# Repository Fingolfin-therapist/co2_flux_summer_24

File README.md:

# Wildfire CO<sub>2</sub> Flux Project - Summer 2024

This directory includes scripts and data for the 2024 Summer Wildfire CO<sub>2</sub> Flux Project. Please see the repository structure section below.

# Repository Structure

|Folder|Description|
|----|----|
|ELT CALIBRATION|Scripts for calibrating ELT S300-3V CO<sub>2</sub> sensors. Ambient colocations are used for ambient sensors. Ambient and closed loop colocations are used for ambient sensors.|
|FLUXES|Scripts for calculating fluxes from datasets.|
|LICOR|Calibration files for LICOR LI-7810.|
|MFC|Calibration and control scripts for Mass Flow Controller (MFC).|
|MODELING|Theoretical applications of box model.|
|DAQ|Hardware and firmware for data acquisition system (DAQ).|

# Contributing

To ensure smooth collaboration and avoid unnecessary merge requests, please follow these simple steps for contribution:

1) Fork the Repository
    - Click the Fork button at the top right of this repository page to create a copy of the repository under your GitHub account.
2) Clone Your Fork
    - Clone your forked repository to your local machine:
    - `git clone https://github.com/BikeLinc/co2_flux_summer_24.git`
    - `cd your-repo`
3) Create a New Branch
    - Create a new branch for your work. Name your branch based on the feature or issue you are working on:
    - `git checkout -b feature/your-feature-name`
4) Make Your Changes
    - Make your changes to the code.
5) Commit Your Changes
    - Commit your changes with a clear and concise commit message:
    - `git add .`
    - `git commit -m "Add description of changes"`
6) Push Your Branch
    - Push your branch to your forked repository:
    - `git push origin feature/your-feature-name`
7) Open a Pull Request
    - Go to the original repository on GitHub. You should see a prompt to open a pull request. Click on it and provide a clear description of your changes.
8) Wait for Review
    - Your pull request will be reviewed. Make any necessary changes based on feedback.

For an extensive guide to git and GitHub, see [GitHub's Git Guide](https://github.com/git-guides).

# Questions

Please email Lincoln (lascheer@fortlewis.edu) for any questions about this repository.

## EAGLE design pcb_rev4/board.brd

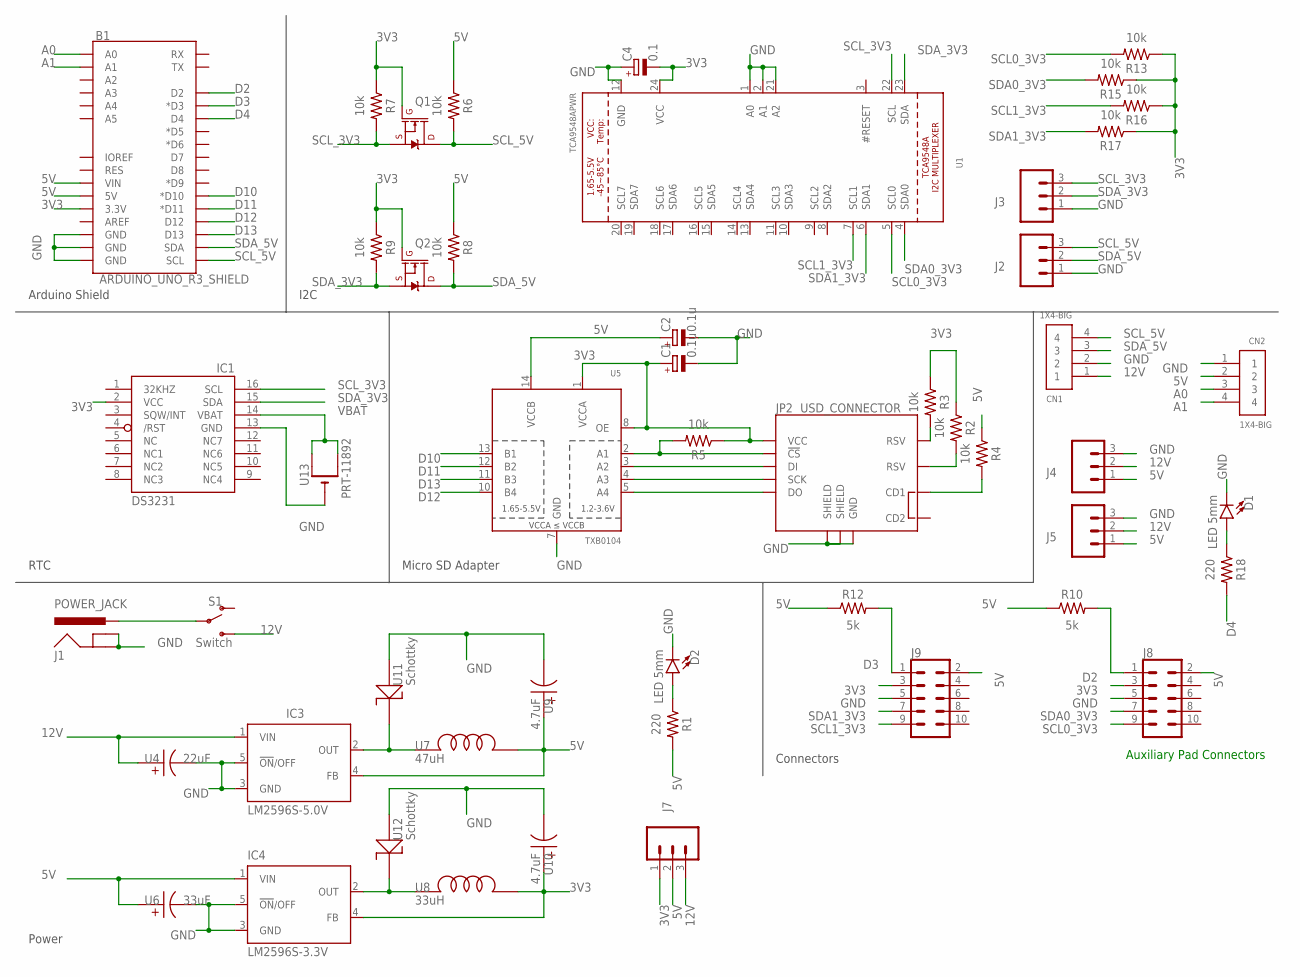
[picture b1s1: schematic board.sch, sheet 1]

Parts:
B1: ARDUINO_UNO_R3_SHIELD; UNO_R3_SHIELD_NOLABELS_LOCK
C1, C2: 0.1u; CAPMP3216X180N
C4: 0.1; CAPMP3216X180N
CN1, CN2: 1X4-BIG; 1X04-BIG
D1, D2: LED 5mm; LED_5MM; PARTNO FLC INVENTORY
IC1: DS3231/SO; SO16W
IC3: LM2596S-5.0V; TO263-5; PARTNO FLC INVENTORY
IC4: LM2596S-3.3V; TO263-5; PARTNO FLC INVENTORY
J1: POWER_JACK; POWER_JACK_PTH; PARTNO FLC INVENTORY
J2, J3, J4, J5, J7: 3-Pin Screw Terminal 5mm; SCREWTERMINAL-5MM-3; PARTNO 2057-EB21A-03-C-ND
J8, J9: 2x6 0.1" Shrouded Female Header; 2X5-SHROUDED_LOCK; PARTNO PRT-08506 and PRT-10650
JP2: USD_CONNECTOR; MICRO-SD-SOCKET-PP
Q1, Q2: 220mA/50V/3.5Ω; SOT23-3
R1, R18: 220; RESC1608X60
R2, R3, R4, R5, R6, R7, R8, R9, R13, R15, R16, R17: 10k; RESC1608X60
R10, R12: 5k; RESC1608X60
S1: Switch; SWITCH_SPDT_PTH_11.6X4.0MM; PARTNO EG2355-ND
U1: TCA9548APWR; TSSOP24
U4: 22uF; CAP_ALUM_22UF_20%_63V_SMD; PARTNO FLC INVENTORY
U5: TXB0104; SO14
U6: 33uF; CAP_ALUM_33UF_20%_63V_SMD; PARTNO FLC INVENTORY
U7: 47uH; FIXED_IND_47UH_3.8A_60_MOHM_SMD; PARTNO FLC INVENTORY
U8: 33uH; FIXED_IND_47UH_3.8A_60_MOHM_SMD; PARTNO FLC INVENTORY
U9, U10: 4.7uF; CAP_ALUM_4.7UF_20%_100V_SMD; PARTNO FLC INVENTORY
U11, U12: Schottky; DIODE_SCHOTTKY_40V_3A_SMC; PARTNO FLC INVENTORY
U13: PRT-11892; CR2032-SMD

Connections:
3V3: B1.3.3V, C1.1 (+), C4.2 (-), IC1.2 (VCC), IC4.4 (FB), J7.1, J8.3, J9.3, JP2.VCC, Q1.1 (G), Q2.1 (G), R2.1, R3.1, R5.1, R7.1, R9.1, R13.1, R15.1, R16.1, R17.1, U1.24 (VCC), U5.1 (VCCA), U5.8 (OE), U8.P$2, U10.P$2
5V: B1.5V, B1.VIN, C2.1 (+), CN2.2, IC3.4 (FB), IC4.1 (VIN), J4.1, J5.1, J7.2, J8.2, J9.2, R1.2, R4.1, R6.1, R8.1, R10.1, R12.1, U5.14 (VCCB), U6.P$2, U7.P$2, U9.P$2
12V: CN1.1, IC3.1 (VIN), J4.2, J5.2, J7.3, S1.3 (S), U4.P$2
!CS_3V3: JP2.CS (!CS), R5.2, U5.2 (A1)
A0: B1.A0, CN2.3
A1: B1.A1, CN2.4
CDSDSD: JP2.CD1, R4.2
D2: B1.D2, J8.1, R10.2
D3: B1.D3 (*D3), J9.1, R12.2
D4: B1.D4, R18.2
D10: B1.D10 (*D10), U5.13 (B1)
D11: B1.D11 (*D11), U5.12 (B2)
D12: B1.D12, U5.10 (B4)
D13: B1.D13, U5.11 (B3)
DI_3V3: JP2.DI, U5.3 (A2)
DO_3V3: JP2.DO, U5.5 (A4)
GND: B1.GND@0 (GND), B1.GND@1 (GND), B1.GND@2 (GND), C1.2 (-), C2.2 (-), C4.1 (+), CN1.2, CN2.1, D1.K (C), D2.K (C), IC1.13 (GND), IC3.3 (GND), IC3.5 (!ON!/OFF), IC4.3 (GND), IC4.5 (!ON!/OFF), J1.GND, J1.GNDBREAK, J2.1, J3.1, J4.3, J5.3, J8.5, J9.5, JP2.GND, JP2.GND1 (SHIELD), JP2.GND3 (SHIELD), U1.1 (A0), U1.2 (A1), U1.12 (GND), U1.21 (A2), U4.P$1, U5.7 (GND), U6.P$1, U9.P$1, U10.P$1, U11.P$1, U12.P$1, U13.-
unnamed: D1.A, R18.1
unnamed: JP2.RSV1 (RSV), R3.2
unnamed: JP2.RSV2 (RSV), R2.2
unnamed: D2.A, R1.1
unnamed: IC3.2 (OUT), U7.P$1, U11.P$2
unnamed: IC4.2 (OUT), U8.P$1, U12.P$2
PWR_IN: J1.PWR, S1.2
SCK_3V3: JP2.SCLK (SCK), U5.4 (A3)
SCL0_3V3: J8.9, R13.2, U1.5 (SCL0)
SCL1_3V3: J9.9, R16.2, U1.7 (SCL1)
SCL_3V3: IC1.16 (SCL), J3.3, Q1.2 (S), R7.2, U1.22 (SCL)
SCL_5V: B1.SCL, CN1.4, J2.3, Q1.3 (D), R6.2
SDA0_3V3: J8.7, R15.2, U1.4 (SDA0)
SDA1_3V3: J9.7, R17.2, U1.6 (SDA1)
SDA_3V3: IC1.15 (SDA), J3.2, Q2.2 (S), R9.2, U1.23 (SDA)
SDA_5V: B1.SDA, CN1.3, J2.2, Q2.3 (D), R8.2
VBAT: IC1.14 (VBAT), U13.+$1 (+), U13.+$2 (+1)

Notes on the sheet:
Arduino Shield
I2C
RTC
Micro SD Adapter
Power
Connectors
Auxiliary Pad Connectors

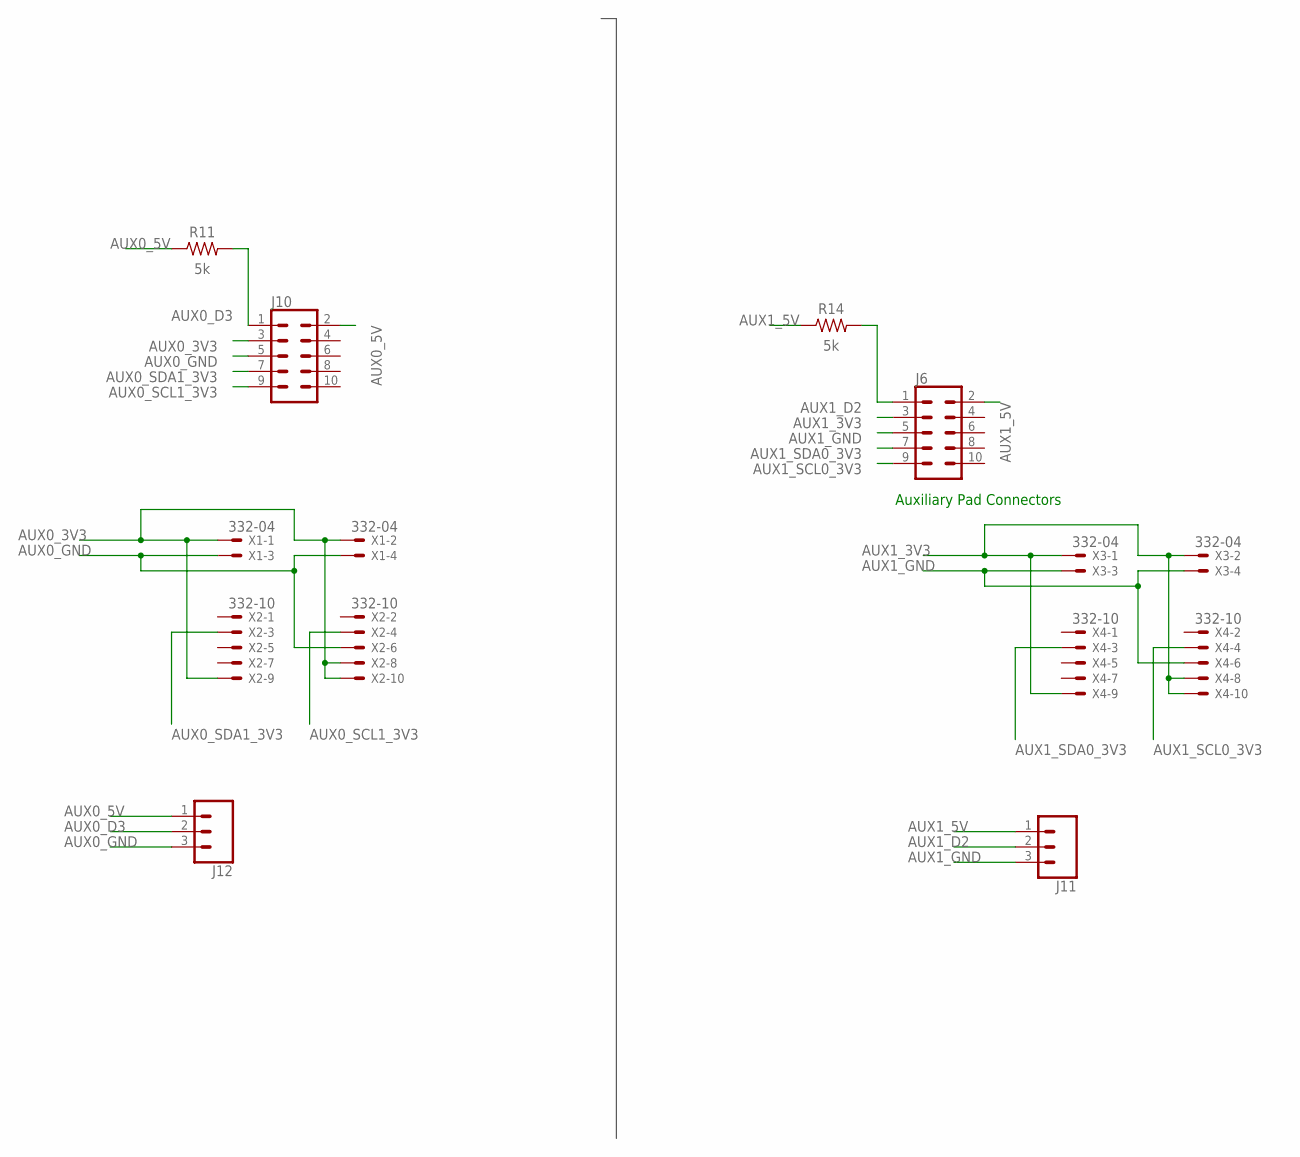
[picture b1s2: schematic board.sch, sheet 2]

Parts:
J6, J10: 2x6 0.1" Shrouded Female Header; 2X5-SHROUDED_LOCK; PARTNO PRT-08506 and PRT-10650
J11, J12: CONN_03; 1X03
R11, R14: 5k; RESC1608X60
X1, X3: 332-04
X2, X4: 332-10

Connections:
AUX0_3V3: J10.3, X1.1, X1.2, X2.8, X2.9, X2.10
AUX0_5V: J10.2, J12.1, R11.1
AUX0_D3: J10.1, J12.2, R11.2
AUX0_GND: J10.5, J12.3, X1.3, X1.4, X2.6
AUX0_SCL1_3V3: J10.9, X2.4
AUX0_SDA1_3V3: J10.7, X2.3
AUX1_3V3: J6.3, X3.1, X3.2, X4.8, X4.9, X4.10
AUX1_5V: J6.2, J11.1, R14.1
AUX1_D2: J6.1, J11.2, R14.2
AUX1_GND: J6.5, J11.3, X3.3, X3.4, X4.6
AUX1_SCL0_3V3: J6.9, X4.4
AUX1_SDA0_3V3: J6.7, X4.3

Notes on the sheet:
Auxiliary Pad Connectors

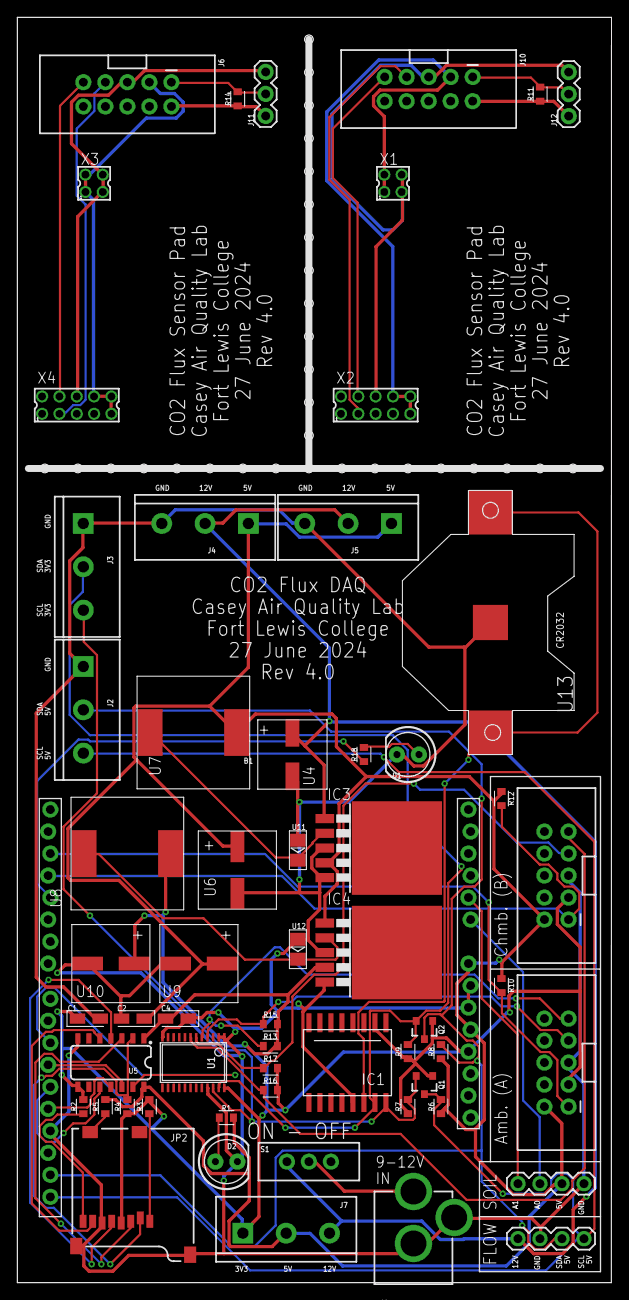
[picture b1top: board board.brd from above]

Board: 2 copper layers, 68.6 x 146.1 mm, 60 parts (0 on the bottom side), 46 nets.

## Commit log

2024-05-13 Add initial ambient colocation data and scripts, and flux test calculation script.
2024-05-13 Add 2.5 LPM MFC Calibration Data and Script
2024-05-15 Applied MFC Calibration Equation to Flux Test Calculations
2024-05-15 Adding Greenhouse Colocation Data
2024-05-15 Added lab colocation data and measurement range calculations.
2024-05-16 Rename and Update MFC Calibration Datasets
2024-05-16 Upload Second PICARRO Ambient Colocation
2024-05-17 Rename Ambient Colocation Datasets
2024-05-17 Edits During Testing
2024-05-19 Update Colocation Path
2024-05-19 Add Ambient Colocation Plots (Greenhouse)
2024-05-20 Upload Failed Flux Test Analysis
2024-05-20 Upload Initial Flux Test Data
2024-05-20 Add Steady State Concentration to Flux Test
2024-05-21 Update Scripts - After 3003 ppm Flux Test
2024-05-21 Update Flux Test Data
2024-05-22 Initial Flux Calculation Script Development - Import Data
2024-05-23 Initial Flux Test Analysis
2024-05-23 Working on Flux Script - Improving Calibration Application
2024-05-24 Updated Flux Script
    Applied Various Calibrations, SLPM to LPM Relization, Linear Calibrations, and Theoretical Simulated Values
2024-05-24 Upload MFC Data Streamer
2024-05-24 Update LPM to SLPM Conversions
2024-05-26 Update Flux Script - Corrected Delivered Fluxes
2024-05-27 Update Flux Script to Include Uncertainty, General Cleanup, and Modularize Code. Add uncertainty to Set-Point Script.
2024-05-28 Revert "Merge branch 'main' of https://github.com/BikeLinc/co2_flux_summer_24"
    This reverts commit b998ad22cd0a1242b409e6b8d43de9fb235fedbc, reversing
    changes made to f07ea22f933707d5448ed3c726b6b5fc94d8dda8.
2024-05-31 3rd Lab Flux Test
2024-06-03 Modularizing Flux Test Script
2024-06-03 Updated Calibrations
2024-06-05 Changing Units of Flux Test and Dilution Set Points
2024-06-05 Compare Calibrations
2024-06-06 Add Backyard Flux Data
2024-06-07 Added MFC slpm to lpm calc. for Set Points - For Sensor Calibration
2024-06-08 Upload Firmware
2024-06-10 Added Firmware
2024-06-10 ignore cache file
2024-06-12 Added Polynomial Fits
2024-06-18 Add Closed Loop Test Folder
2024-06-19 Add Extended Closed Loop Dataset
2024-06-20 update for A&WM poster rought draft
2024-06-23 Remove Picarro.txt - Error
2024-06-23 Add large file to .gitignore
2024-06-23 Prepare Plots for A&WMA
2024-06-28 Add PCB Rev4 Files
2024-06-28 Update Firmware
2024-07-03 Update Firmware for Breadboard Deployment; Upload Initial Breadboard Deployment Data
2024-07-03 Update README and Folder Structure
2024-07-05 Create Miles.txt.txt
    ADD SUMMARY
2024-08-01 NO Changes
    NO changes, grabbing this code for the Arduino issues that happened July 31, 2024

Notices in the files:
parts and their libraries:
SparkFun-Boards: Licensing: Creative Commons ShareAlike 4.0 International - https://creativecommons.org/licenses/by-sa/4.0
SparkFun-Connectors: Licensing: CC v3.0 Share-Alike You are welcome to use this library for commercial purposes.
